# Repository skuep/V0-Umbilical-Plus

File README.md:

# Note that this Repo is the 'Plus' Version of the original V0-Umbilical
The original version was created by GitHub user timmit99 and can be found in the official Voron-Hardware repository.

The 'Plus' version of the V0-Umbilical features an integrated ADXL345 Accelerometer that can be used for Input Shaper Tuning.
The Molex MicroFit connector was changed from a 14-pin to 20-pin version to acommodate the additional wires for the ADXL345.

In the following, the changes to the original README from timmit99 is given. Please read the README in the original project first.

 | 
|:---:|:---:|

### Frame PCB BOM
| Part      | Quantity | Notes | LCSC Part Number | Link |
| ----------- | :-: | ----------- | ----------- |----------- |
| 20 Pin Socket   |  1 | MOLEX 430452012 | C485575   | https://www.lcsc.com/product-detail/Wire-To-Board-Wire-To-Wire-Connector_MOLEX-430452012_C485575.html |
| SMD Thermistor  |  1 | 100K 0805 Thermistor | C143680   | https://lcsc.com/product-detail/NTC-Thermistors_Vishay-Intertech-NTCS0805E3104FXT_C143680.html |
| 2 pin JST XH    |  5 | 2.5mm pitch | C158012   | https://lcsc.com/product-detail/Wire-To-Board-Wire-To-Wire-Connector_JST-Sales-America-B2B-XH-A-LF-SN_C158012.html |
| 3 pin JST XH    |  2 | 2.5mm pitch | C144394   | https://lcsc.com/product-detail/Wire-To-Board-Wire-To-Wire-Connector_JST-Sales-America-B3B-XH-A-LF-SN_C144394.html |
| 4 pin JST XH    |  3 | 2.5mm pitch | C144395   | https://lcsc.com/product-detail/Wire-To-Board-Wire-To-Wire-Connector_JST-Sales-America-B4B-XH-A-LF-SN_C144395.html |
| 6 pin JST XH    |  1 | 2.5mm pitch | C144397   | https://www.lcsc.com/product-detail/Wire-To-Board-Wire-To-Wire-Connector_JST-Sales-America_B6B-XH-A-LF-SN_JST-Sales-America-B6B-XH-A-LF-SN_C144397.html |
| Screw Terminal  |  1 | 5.08mm pitch | C8465     | https://lcsc.com/product-detail/Screw-terminal_Ningbo-Kangnex-Elec-WJ500V-5-08-2P_C8465.html |

### Optional Parts
| Part      | Quantity | Notes | LCSC Part Number | Link |
| ----------- | :-: | ----------- | ----------- |----------- |
| 0805 10uF Capacitor  |  3 | Use if using BARE neopixel IC's. Strips have these already. | C17024     | https://lcsc.com/product-detail/Multilayer-Ceramic-Capacitors-MLCC-SMD-SMT_Samsung-Electro-Mechanics-CL21A106KPFNNNE_C17024.html |
----

### Toolhead PCB BOM
| Part      | Quantity | Notes | LCSC Part Number | Link |
| ----------- | :-: | ----------- | ----------- |----------- |
| 20 Pin Socket (Right Angle)   | 1 |  Molex 430452000  | C485576   | https://www.lcsc.com/product-detail/Wire-To-Board-Wire-To-Wire-Connector_MOLEX-430452000_C485576.html |
| 2 pin JST XH    | 6 |  B2B-XH  | C158012   | https://lcsc.com/product-detail/Wire-To-Board-Wire-To-Wire-Connector_JST-Sales-America-B2B-XH-A-LF-SN_C158012.html |
| 4 pin JST XH    | 1 |  B4B-XH  | C144395   | https://lcsc.com/product-detail/Wire-To-Board-Wire-To-Wire-Connector_JST-Sales-America-B4B-XH-A-LF-SN_C144395.html |
| LP2985-33DBVR   | 1 | 3.3V LDO | C95414    | https://www.lcsc.com/product-detail/Linear-Voltage-Regulators-LDO_Texas-Instruments-LP2985-33DBVR_C95414.html |
| ADXL345BCCZ     | 1 | Accelerometer | C9667     | https://www.lcsc.com/product-detail/Motion-Sensors-Accelerometers_Analog-Devices-ADXL345BCCZ-RL7_C9667.html |
| 10 Ohm Resistor | 2 | 0603 size |  C22859  | https://www.lcsc.com/product-detail/Chip-Resistor-Surface-Mount_UNI-ROYAL-Uniroyal-Elec-0603WAF100JT5E_C22859.html |
| 10 kOhm Resistor| 1 | 0603 size |   C25804 | https://www.lcsc.com/product-detail/Chip-Resistor-Surface-Mount_UNI-ROYAL-Uniroyal-Elec-0603WAF1002T5E_C25804.html |
| 4.7uF Capacitor | 2 | 0603 size |  C19666  | https://www.lcsc.com/product-detail/Multilayer-Ceramic-Capacitors-MLCC-SMD-SMT_Samsung-Electro-Mechanics-CL10A475KO8NNNC_C19666.html |
| 10nF Capacitor  | 2 | 0603 size |  C57112  | https://lcsc.com/product-detail/Multilayer-Ceramic-Capacitors-MLCC-SMD-SMT_10nF-103-10-50V_C57112.html/?href=jlc-SMT |
---

Corresponding CPL and BOM files are included in the repository. Using these files you can easily get yourself a ready-made assembled PCB from JLCPCB so you don't have to have the skills to solder the fine-pitch and 0603 packages.

## Umbilical cable

The Umbilical cable is a 220-240mm dual ended 20P (2x10) microfit cable. The connectors are wired 1:1 so pin 1 connects to pin 1 and so forth for all 20 pins.

### Cable BOM
| Part      | Quantity | Notes | LCSC Part Number | Link |
| ----------- | :-: | ----------- | ----------- |----------- |
| 20 Pin Plug     | 2  | Molex 430252000 | C485324   | https://lcsc.com/product-detail/Connectors-Housings_MOLEX-430252000_C485324.html |
| Crimps 20 AWG   | 12 | Molex 430300001/430300007 | C259786   | https://lcsc.com/product-detail/Line-Pressing-Terminals_MOLEX-430300001_C259786.html |
| Crimps 26 AWG   | 28 | Molex 430300004/430300010 | C259765   | https://lcsc.com/product-detail/Line-Pressing-Terminals_MOLEX-430300004_C259765.html |
| 20AWG Wire      | 6  | 220mm Sections  |    | PTFE/Silicone/Hefulon for motion rated, PVC *could* work since it isn't constraind to a cable chain |
| 26AWG Wire      | 14 |   |    |  |

MicroFit connectors support two different ranges of conductor thickness using different wire crimp ferrules. I recommend that you realize the stepper motor and heater wires with 20AWG wire (0.5mm²) and the remaining wires in 26AWG wire (0.14mm²) to save on weight and accelerated mass.

## Hints and Remarks
### Extruder Stepper Direction
The umbilical cable reverses the stepper rotation direction. I.e. you need to invert the DIR pin of the extruder motor in your printer.cfg file.

    [extruder]
    ....
    dir_pin: PB4 # Add ! (or remove ! if already there) before 'PB4'
    ....

### Mounting the Toolhead PCB
The umbilical toolhead PCB uses heat stake inserts in order to mount it to the motor screws. In some cases (i.e. LDO motors), the extruder motor already has an additional thread, which has to be either removed by drilling the motor holes with a 3mm spiral drill. If you do not want to drill into the motor, you can use M3x10 captive screws, which are unfortunately hard to find. These screws have a narrowed section and a short thread at the tip so they only 'grab' the thread of the heat stake inserts.

### Additional chamber thermistor on SKR mini V2.0
If you are using the SKR mini V2.0 board and you want to connect the chamber thermistor, you can use Timmit99's expansion board (https://github.com/VoronDesign/Voron-Hardware/tree/master/SKR-Mini_TFT_Thermistor_Board). 

If you want an easier and faster solution, you can move the Z-STOP endswitch pin and connect it the E0-STOP pin using a simple self-made JST 2-pin to 3-pin adapter (See Photos folder) or by removing the crimp pins from the 2-pin JST and insert them into the housing of a 3-pin JST header. Once the Z-STOP pin is freed up, you can use it for your thermistor. This method needs the following printer.cfg changes:

    [stepper_z]
    ...
    endstop_pin: ^PC15 # Conversion for additional thermistor (use E0-STOP for Z-STOP)
    ...
    
    [temperature_sensor chamber]
    sensor_type: Generic 3950
    sensor_pin: PC2
    gcode_id: C
    pullup_resistor: 10000

### Connecting the ADXL345 to a Raspberry Pi
The ADXL345 circuit on the toolhead PCB includes a R-C filter and a 3.3V low-dropout regulator to deliver a clean power supply. Thus you can use the official drawings shown in the corresponding docs (https://www.klipper3d.org/Measuring_Resonances.html), with one small change. You need to connect VCC to +5V (Pin 2 or Pin 4) instead of 3.3V (Pin 1) on the Raspberry Pi extension header (See Photos folder). Then follow the official docs for setting the resonance measurement up.

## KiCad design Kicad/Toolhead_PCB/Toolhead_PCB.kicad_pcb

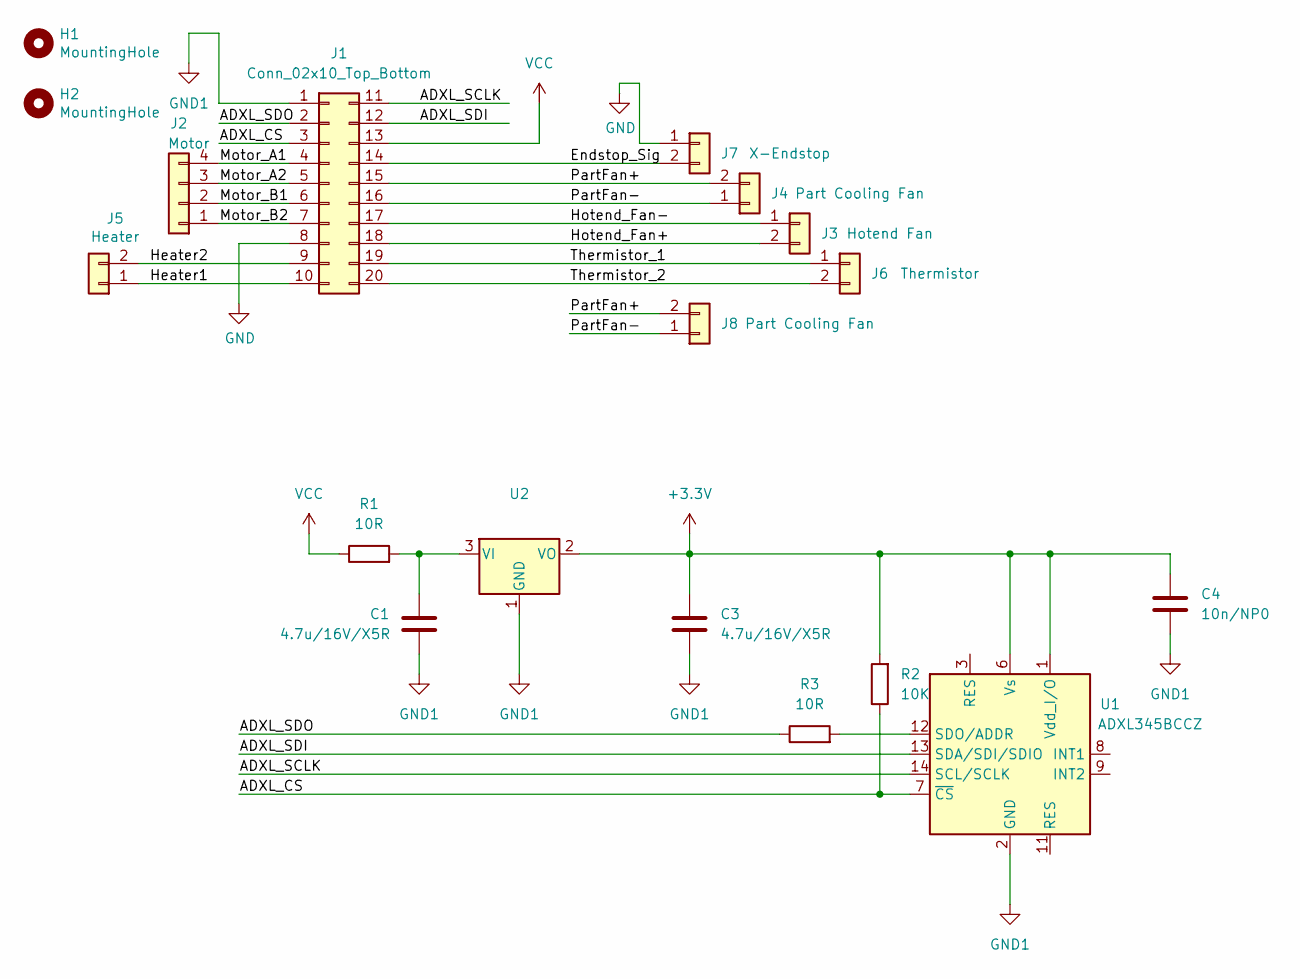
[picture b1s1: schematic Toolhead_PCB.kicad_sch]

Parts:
C1, C3: 4.7u/16V/X5R; C_0603_1608Metric
C4: 10n/NP0; C_0603_1608Metric
H1, H2: MountingHole; MountingHole_3.2mm_M3
J1: Conn_02x10_Top_Bottom; Molex_Micro-Fit_3.0_43045-2000_2x10_P3.00mm_Horizontal
J2: Motor; JST_XH_B4B-XH-A_1x04_P2.50mm_Vertical
J3: Hotend Fan; JST_XH_B2B-XH-A_1x02_P2.50mm_Vertical
J4, J8: Part Cooling Fan; JST_XH_B2B-XH-A_1x02_P2.50mm_Vertical
J5: Heater; JST_XH_B2B-XH-A_1x02_P2.50mm_Vertical
J6: Thermistor; JST_XH_B2B-XH-A_1x02_P2.50mm_Vertical
J7: X-Endstop; JST_XH_B2B-XH-A_1x02_P2.50mm_Vertical
R1, R3: 10R; R_0603_1608Metric
R2: 10K; R_0603_1608Metric
U1: ADXL345BCCZ; LGA-14_3x5mm_P0.8mm_LayoutBorder1x6y
U2: (no value)

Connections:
+3V3: C3.1, C4.1, R2.2, U1.1 (Vdd_I/O), U1.6 (Vs), U2.2 (VO)
/ADXL_CS: J1.3, R2.1, U1.7 (~CS)
/ADXL_SCLK: J1.11, U1.14 (SCL/SCLK)
/ADXL_SDI: J1.12, U1.13 (SDA/SDI/SDIO)
/ADXL_SDO: J1.2, R3.1
/Endstop_Sig: J1.14, J7.2
/Heater1: J1.10, J5.1
/Heater2: J1.9, J5.2
/Hotend_Fan+: J1.18, J3.2
/Hotend_Fan-: J1.17, J3.1
/Motor_A1: J1.4, J2.4
/Motor_A2: J1.5, J2.3
/Motor_B1: J1.6, J2.2
/Motor_B2: J1.7, J2.1
/PartFan+: J1.15, J4.2, J8.2
/PartFan-: J1.16, J4.1, J8.1
/Thermistor_1: J1.19, J6.1
/Thermistor_2: J1.20, J6.2
GND: J1.8, J7.1
GND1: C1.2, C3.2, C4.2, J1.1, U1.2 (GND), U1.4 (GND), U1.5 (GND), U2.1 (GND)
unnamed: C1.1, R1.2, U2.3 (VI)
unnamed: R3.2, U1.12 (SDO/ADDR)
VCC: J1.13, R1.1

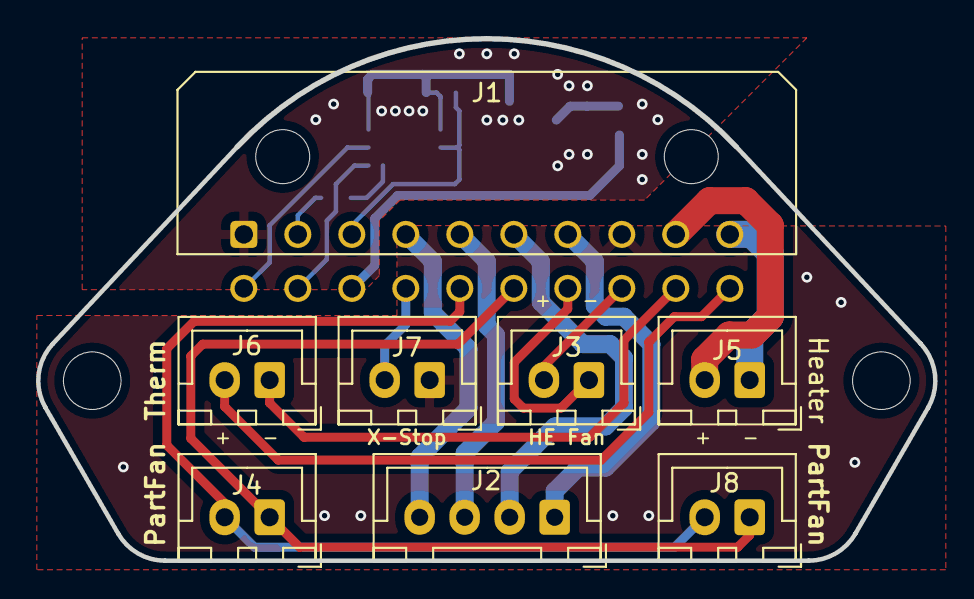
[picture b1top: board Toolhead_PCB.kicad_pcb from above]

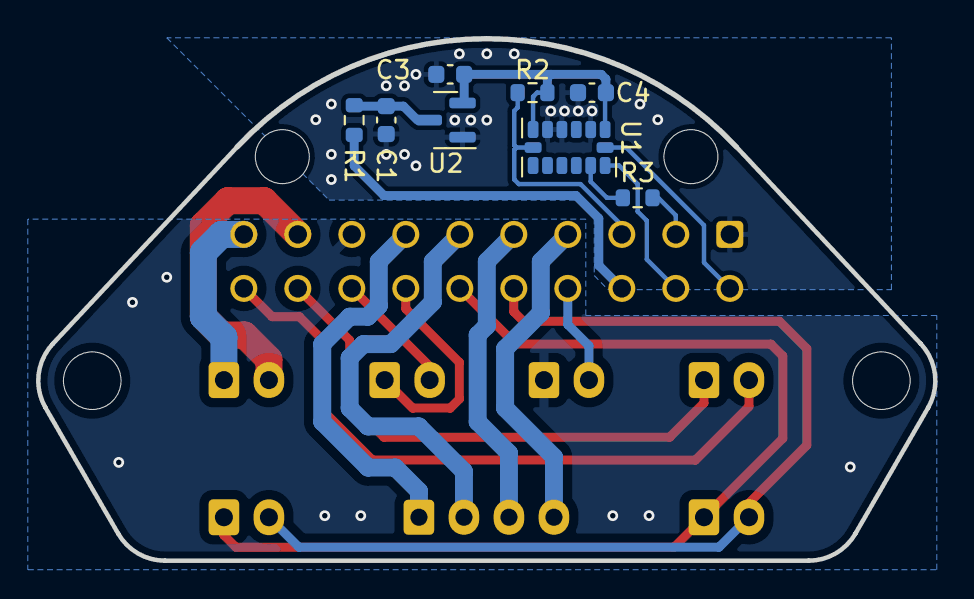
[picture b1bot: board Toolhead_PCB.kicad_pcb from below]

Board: 2 copper layers, 49.8 x 29.0 mm, 18 parts (8 on the bottom side), 23 nets.

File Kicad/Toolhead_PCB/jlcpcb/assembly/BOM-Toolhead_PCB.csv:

Comment,Designator,Footprint,LCSC
4.7u/16V/X5R,"C1,C3",C_0603_1608Metric,C19666
10R,"R1,R3",R_0603_1608Metric,C22859
10K,R2,R_0603_1608Metric,C25804
10n/NP0,"C2,C4",C_0603_1608Metric,C57112
LP2985-33DBVR,U2,SOT-23-5,C95414
ADXL345BCCZ,U1,LGA-14_3x5mm_P0.8mm_LayoutBorder1x6y,C9667
Conn_02x10_Top_Bottom,J1,Molex_Micro-Fit_3.0_43045-2000_2x10_P3.00mm_Horizontal,
X-Endstop,J7,JST_XH_B2B-XH-A_1x02_P2.50mm_Vertical,
Heater,J5,JST_XH_B2B-XH-A_1x02_P2.50mm_Vertical,
Hotend Fan,J3,JST_XH_B2B-XH-A_1x02_P2.50mm_Vertical,
Thermistor,J6,JST_XH_B2B-XH-A_1x02_P2.50mm_Vertical,
Part Cooling Fan,J4,JST_XH_B2B-XH-A_1x02_P2.50mm_Vertical,
Motor,J2,JST_XH_B4B-XH-A_1x04_P2.50mm_Vertical,
Part Cooling Fan,J8,JST_XH_B2B-XH-A_1x02_P2.50mm_Vertical,

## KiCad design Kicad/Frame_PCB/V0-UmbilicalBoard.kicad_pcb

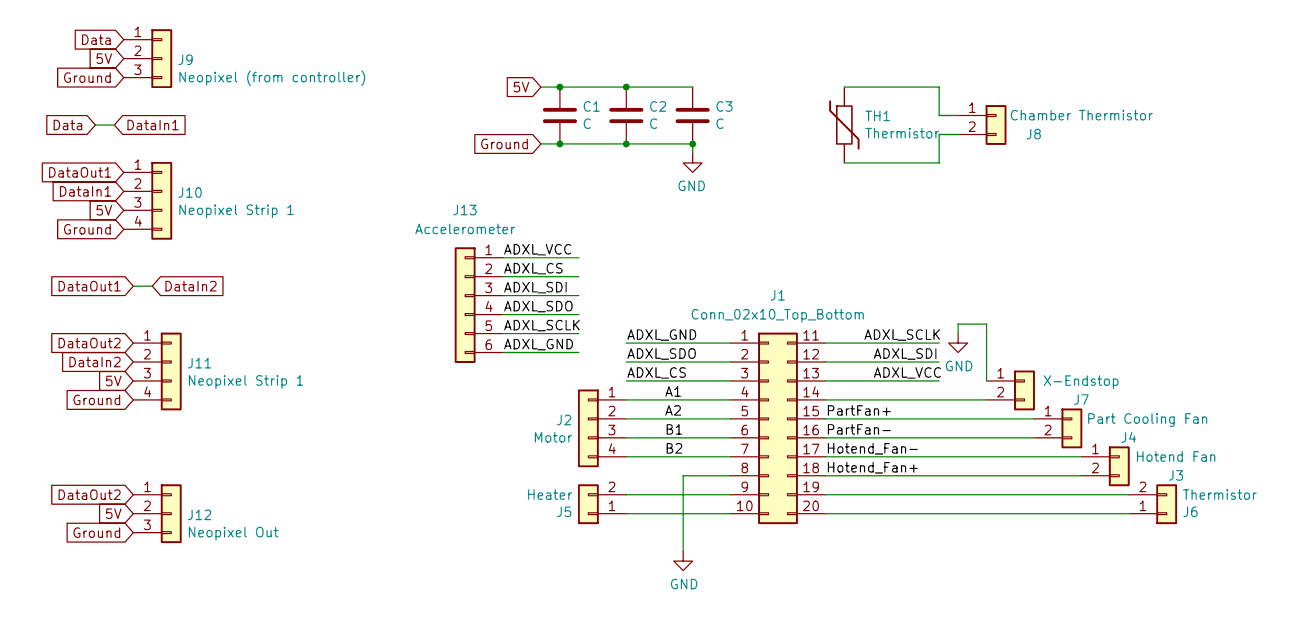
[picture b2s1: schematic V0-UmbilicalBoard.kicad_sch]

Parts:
C1, C2, C3: C; C_0805_2012Metric_Pad1.18x1.45mm_HandSolder
J1: Conn_02x10_Top_Bottom; Molex_Micro-Fit_3.0_43045-2012_2x10_P3.00mm_Vertical
J2: Motor; JST_XH_B4B-XH-A_1x04_P2.50mm_Vertical
J3: Hotend Fan; JST_XH_B2B-XH-A_1x02_P2.50mm_Vertical
J4: Part Cooling Fan; JST_XH_B2B-XH-A_1x02_P2.50mm_Vertical
J5: Heater; TerminalBlock_Phoenix_MKDS-1,5-2-5.08_1x02_P5.08mm_Horizont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
J6: Thermistor; JST_XH_B2B-XH-A_1x02_P2.50mm_Vertical
J7: X-Endstop; JST_XH_B2B-XH-A_1x02_P2.50mm_Vertical
J8: Chamber Thermistor; JST_XH_B2B-XH-A_1x02_P2.50mm_Vertical
J9: Neopixel (from controller); JST_XH_B3B-XH-A_1x03_P2.50mm_Vertical
J10, J11: Neopixel Strip 1; JST_XH_B4B-XH-A_1x04_P2.50mm_Vertical
J12: Neopixel Out; JST_XH_B3B-XH-A_1x03_P2.50mm_Vertical
J13: Accelerometer; JST_XH_B6B-XH-A_1x06_P2.50mm_Vertical
TH1: Thermistor; R_0805_2012Metric_Pad1.20x1.40mm_HandSolder

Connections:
5V: C1.1, C2.1, C3.1, J9.2, J10.3, J11.3, J12.2
/A1: J1.4, J2.1
/A2: J1.5, J2.2
/ADXL_CS: J1.3, J13.2
/ADXL_GND: J1.1, J13.6
/ADXL_SCLK: J1.11, J13.5
/ADXL_SDI: J1.12, J13.3
/ADXL_SDO: J1.2, J13.4
/ADXL_VCC: J1.13, J13.1
/B1: J1.6, J2.3
/B2: J1.7, J2.4
/Hotend_Fan+: J1.18, J3.2
/Hotend_Fan-: J1.17, J3.1
/PartFan+: J1.15, J4.1
/PartFan-: J1.16, J4.2
Data: J9.1, J10.2
DataIn2: J10.1, J11.2
DataOut2: J11.1, J12.1
Ground: C1.2, C2.2, C3.2, J1.8, J7.1, J9.3, J10.4, J11.4, J12.3
unnamed: J1.9, J5.2
unnamed: J1.10, J5.1
unnamed: J1.14, J7.2
unnamed: J1.19, J6.2
unnamed: J1.20, J6.1
unnamed: J8.1, TH1.1
unnamed: J8.2, TH1.2

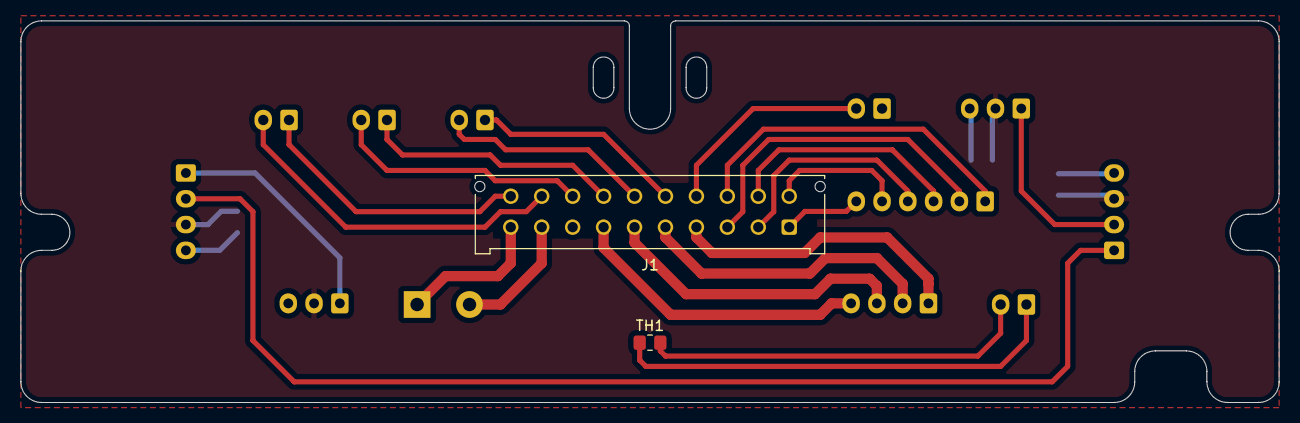
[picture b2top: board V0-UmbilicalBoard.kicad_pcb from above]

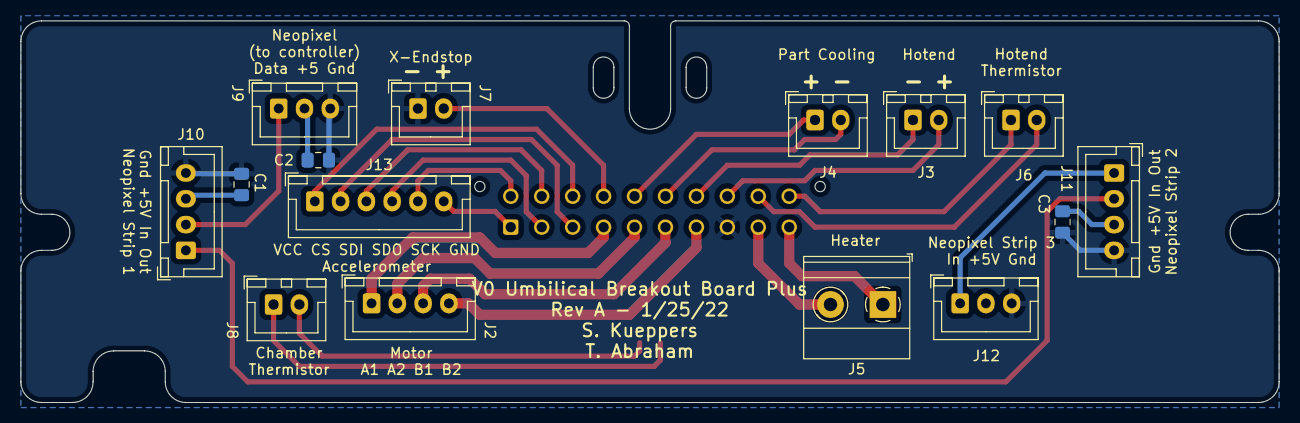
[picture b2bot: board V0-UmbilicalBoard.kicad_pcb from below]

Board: 2 copper layers, 122.0 x 37.0 mm, 17 parts (15 on the bottom side), 26 nets.

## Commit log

2022-01-30 Removed CSV files from gitignore
2022-01-30 Added missing 3D model for Molex MicroFit
2022-01-30 Copy over Frame PCB cover STL
2022-01-30 Changed Micro Fit connector to 20 pin type and added 6-pin XH for accelerometer. Changed silkscreen text
2022-01-30 Updated part number of ICs
2022-01-30 Added BOM/CPL file for JLCPCB ordering
2022-01-30 Update README.md
    Added image of Toolhead PCB
2022-01-30 Minor changes, added new schematic and project file
2022-01-30 Copy V0-Umbilical to V0-Umbilical-Plus
2022-01-30 Regenerated gerbers, added PnP and BOM
2022-01-30 Adapted README.md
2022-01-30 Update README.md
    Adapted README to Plus version
2022-01-30 Updated Gerber files
2022-01-30 Added accelerometer to Toolhead PCB, modified connector to 20-pin Molex Micro Fit
2022-01-30 Added PnP file
2022-01-30 Added BOM file
2022-01-30 Added images of PCBs
2022-01-30 Saved Export settings
2022-01-30 Fixed broken image link
2022-03-13 Update README.md
    Added Hints and Remarks section
2022-03-13 Added schematics for pinout
2022-03-13 Added STL of 3D printed Toolhead Mount
2022-03-13 Added Step Models of PCBs
2022-03-13 Added 3D export paths
2022-03-13 Added Photographs
2022-03-29 Switch LDO to more available part. Migrate to JLCPBC Kicad plugin for maintainability
2022-03-29 Fix part rotations
2022-03-29 Updated README.md
    Added photograph of toolhead
2022-04-04 Added STL of modified frame PCB cover
2022-04-04 Fixed wrong number of required wires
2022-04-05 Moved over to the KiCAD JLCPCB plugin
2023-01-02 Added toolhead STL for Mini After LGX Lite
